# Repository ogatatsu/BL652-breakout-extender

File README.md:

# BL652-breakout-extender

[BL652-breakout](https://github.com/ogatatsu/BL652-breakout)を単3電池1本で動作させるための拡張基板。

## 部品

| Name | Description | Manufacturer
----|----|----
| U1 | TPS610986_Module | https://www.switch-science.com/catalog/3659/ |
| SW1 | Slide Switch, SS-12D00-G5| Zhejiang Jianfu Electronics Co., Ltd |
| BT1 | Battery Holder, BH-311-1P24| COMFORTABLE ELECTRONIC CO., LTD |

## License

https://creativecommons.org/licenses/by/4.0/

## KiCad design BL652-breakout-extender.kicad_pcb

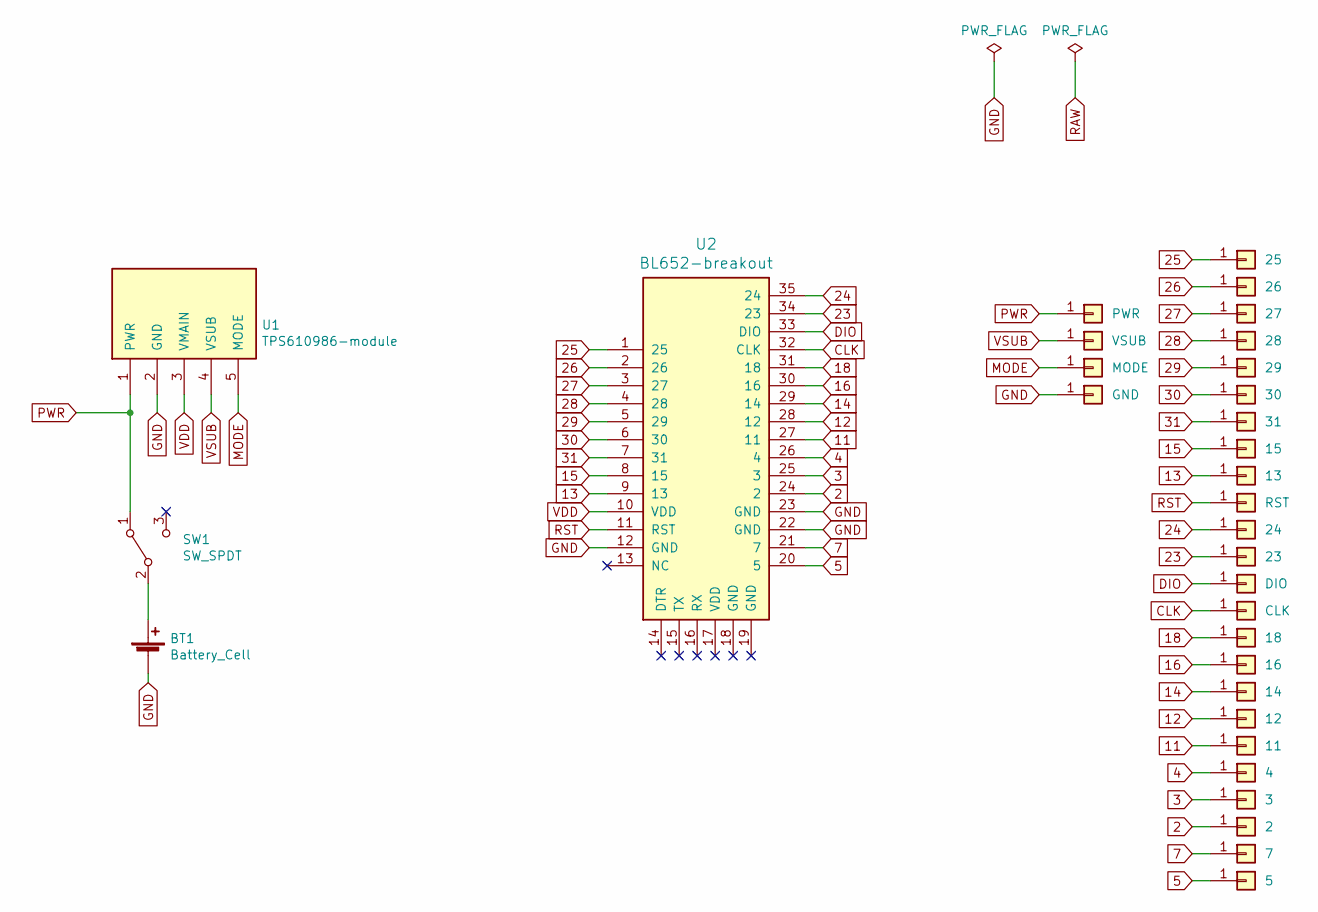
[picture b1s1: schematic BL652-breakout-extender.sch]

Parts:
BT1: Battery_Cell; BH-311-1P24
J3: PWR; Wirepad
J4: VSUB; Wirepad
J5: MODE; Wirepad
J6: GND; Wirepad
J7: 25; Wirepad
J8: 26; Wirepad
J9: 27; Wirepad
J10: 28; Wirepad
J11: 29; Wirepad
J12: 30; Wirepad
J13: 31; Wirepad
J14: 15; Wirepad
J15: 13; Wirepad
J16: RST; Wirepad
J17: 24; Wirepad
J18: 23; Wirepad
J19: DIO; Wirepad
J20: CLK; Wirepad
J21: 18; Wirepad
J22: 16; Wirepad
J23: 14; Wirepad
J24: 12; Wirepad
J25: 11; Wirepad
J26: 4; Wirepad
J27: 3; Wirepad
J28: 2; Wirepad
J29: 7; Wirepad
J30: 5; Wirepad
SW1: SW_SPDT
U1: TPS610986-module
U2: BL652-breakout

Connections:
2: J28.1, U2.24 (2)
3: J27.1, U2.25 (3)
4: J26.1, U2.26 (4)
5: J30.1, U2.20 (5)
7: J29.1, U2.21 (7)
11: J25.1, U2.27 (11)
12: J24.1, U2.28 (12)
13: J15.1, U2.9 (13)
14: J23.1, U2.29 (14)
15: J14.1, U2.8 (15)
16: J22.1, U2.30 (16)
18: J21.1, U2.31 (18)
23: J18.1, U2.34 (23)
24: J17.1, U2.35 (24)
25: J7.1, U2.1 (25)
26: J8.1, U2.2 (26)
27: J9.1, U2.3 (27)
28: J10.1, U2.4 (28)
29: J11.1, U2.5 (29)
30: J12.1, U2.6 (30)
31: J13.1, U2.7 (31)
CLK: J20.1, U2.32 (CLK)
DIO: J19.1, U2.33 (DIO)
GND: BT1.2 (-), J6.1, U1.2 (GND), U2.12 (GND), U2.22 (GND), U2.23 (GND)
MODE: J5.1, U1.5 (MODE)
unnamed: BT1.1 (+), SW1.2 (B)
PWR: J3.1, SW1.1 (A), U1.1 (PWR)
RST: J16.1, U2.11 (RST)
VDD: U1.3 (VMAIN), U2.10 (VDD)
VSUB: J4.1, U1.4 (VSUB)

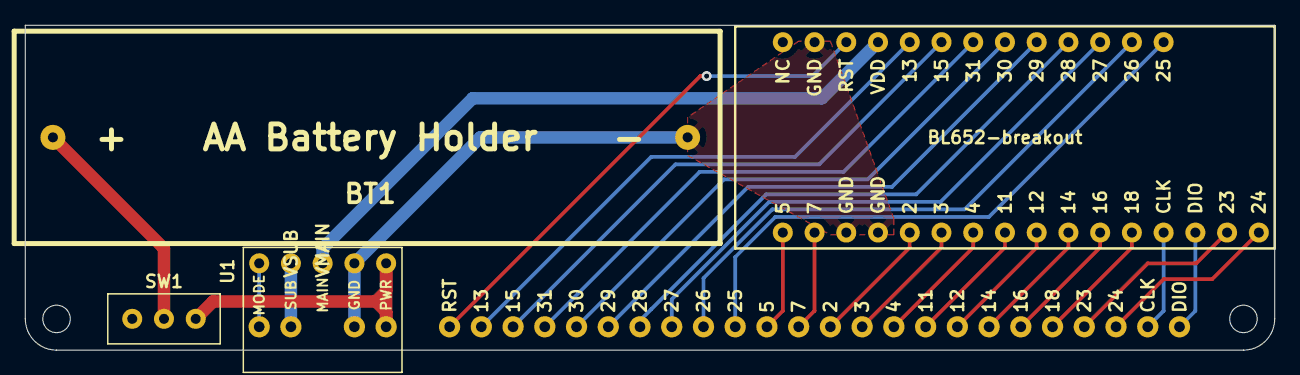
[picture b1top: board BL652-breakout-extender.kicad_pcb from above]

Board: 2 copper layers, 100.0 x 26.0 mm, 34 parts (0 on the bottom side), 30 nets.

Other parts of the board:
REF1, REF2: MountingHole_2.2mm_M2

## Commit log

2019-04-21 add schematic
2019-04-21 add Image
